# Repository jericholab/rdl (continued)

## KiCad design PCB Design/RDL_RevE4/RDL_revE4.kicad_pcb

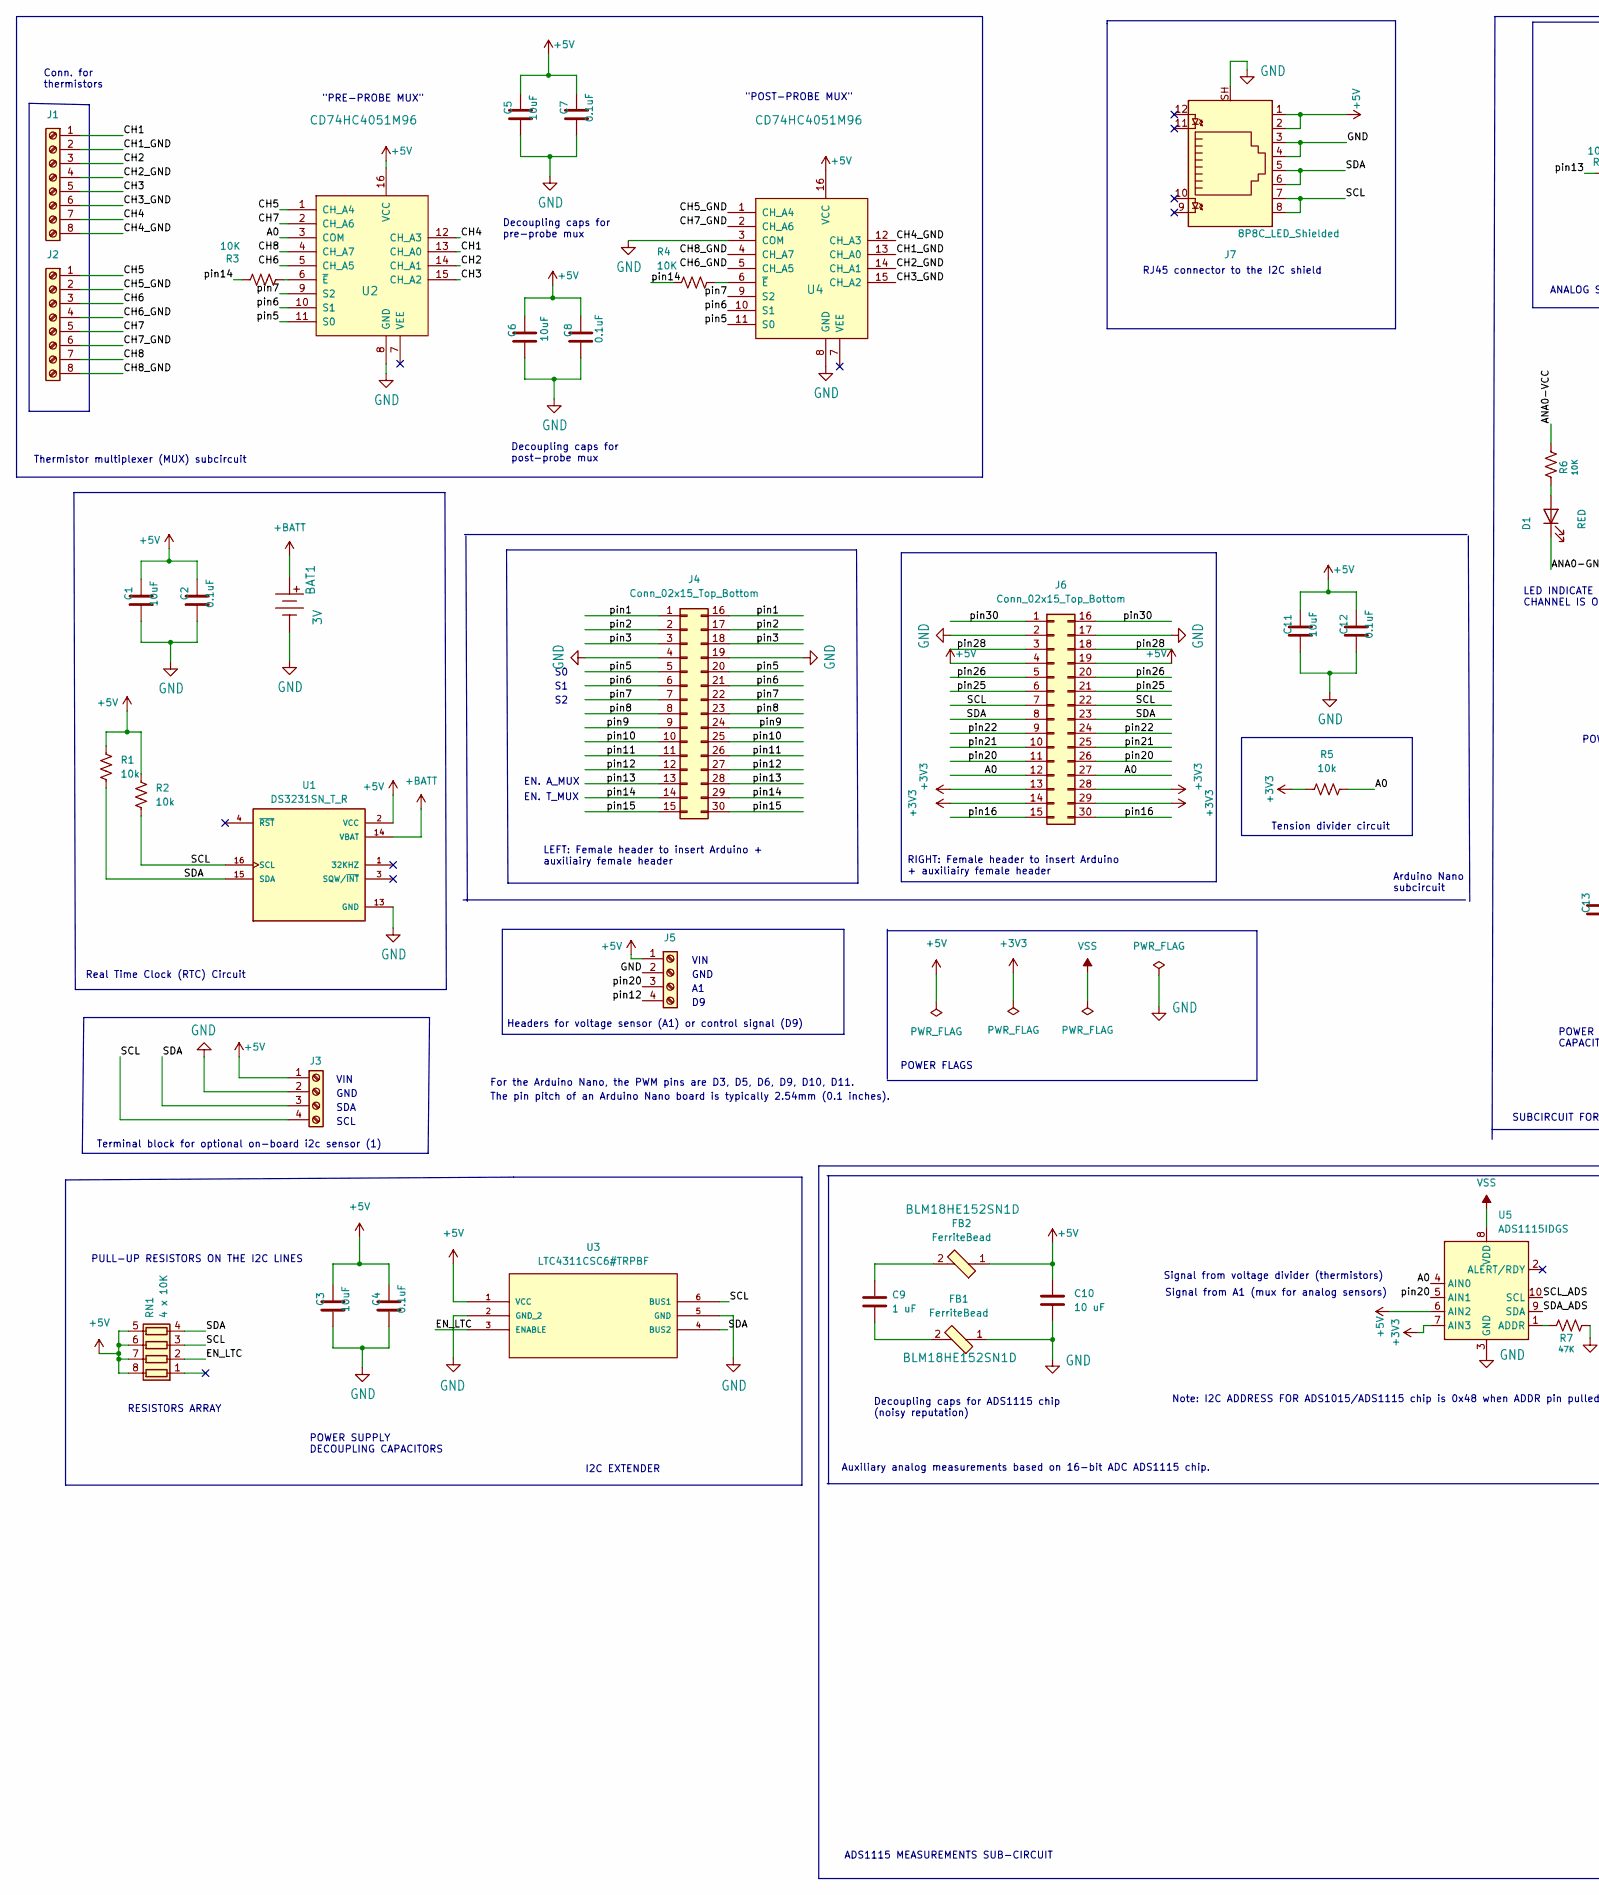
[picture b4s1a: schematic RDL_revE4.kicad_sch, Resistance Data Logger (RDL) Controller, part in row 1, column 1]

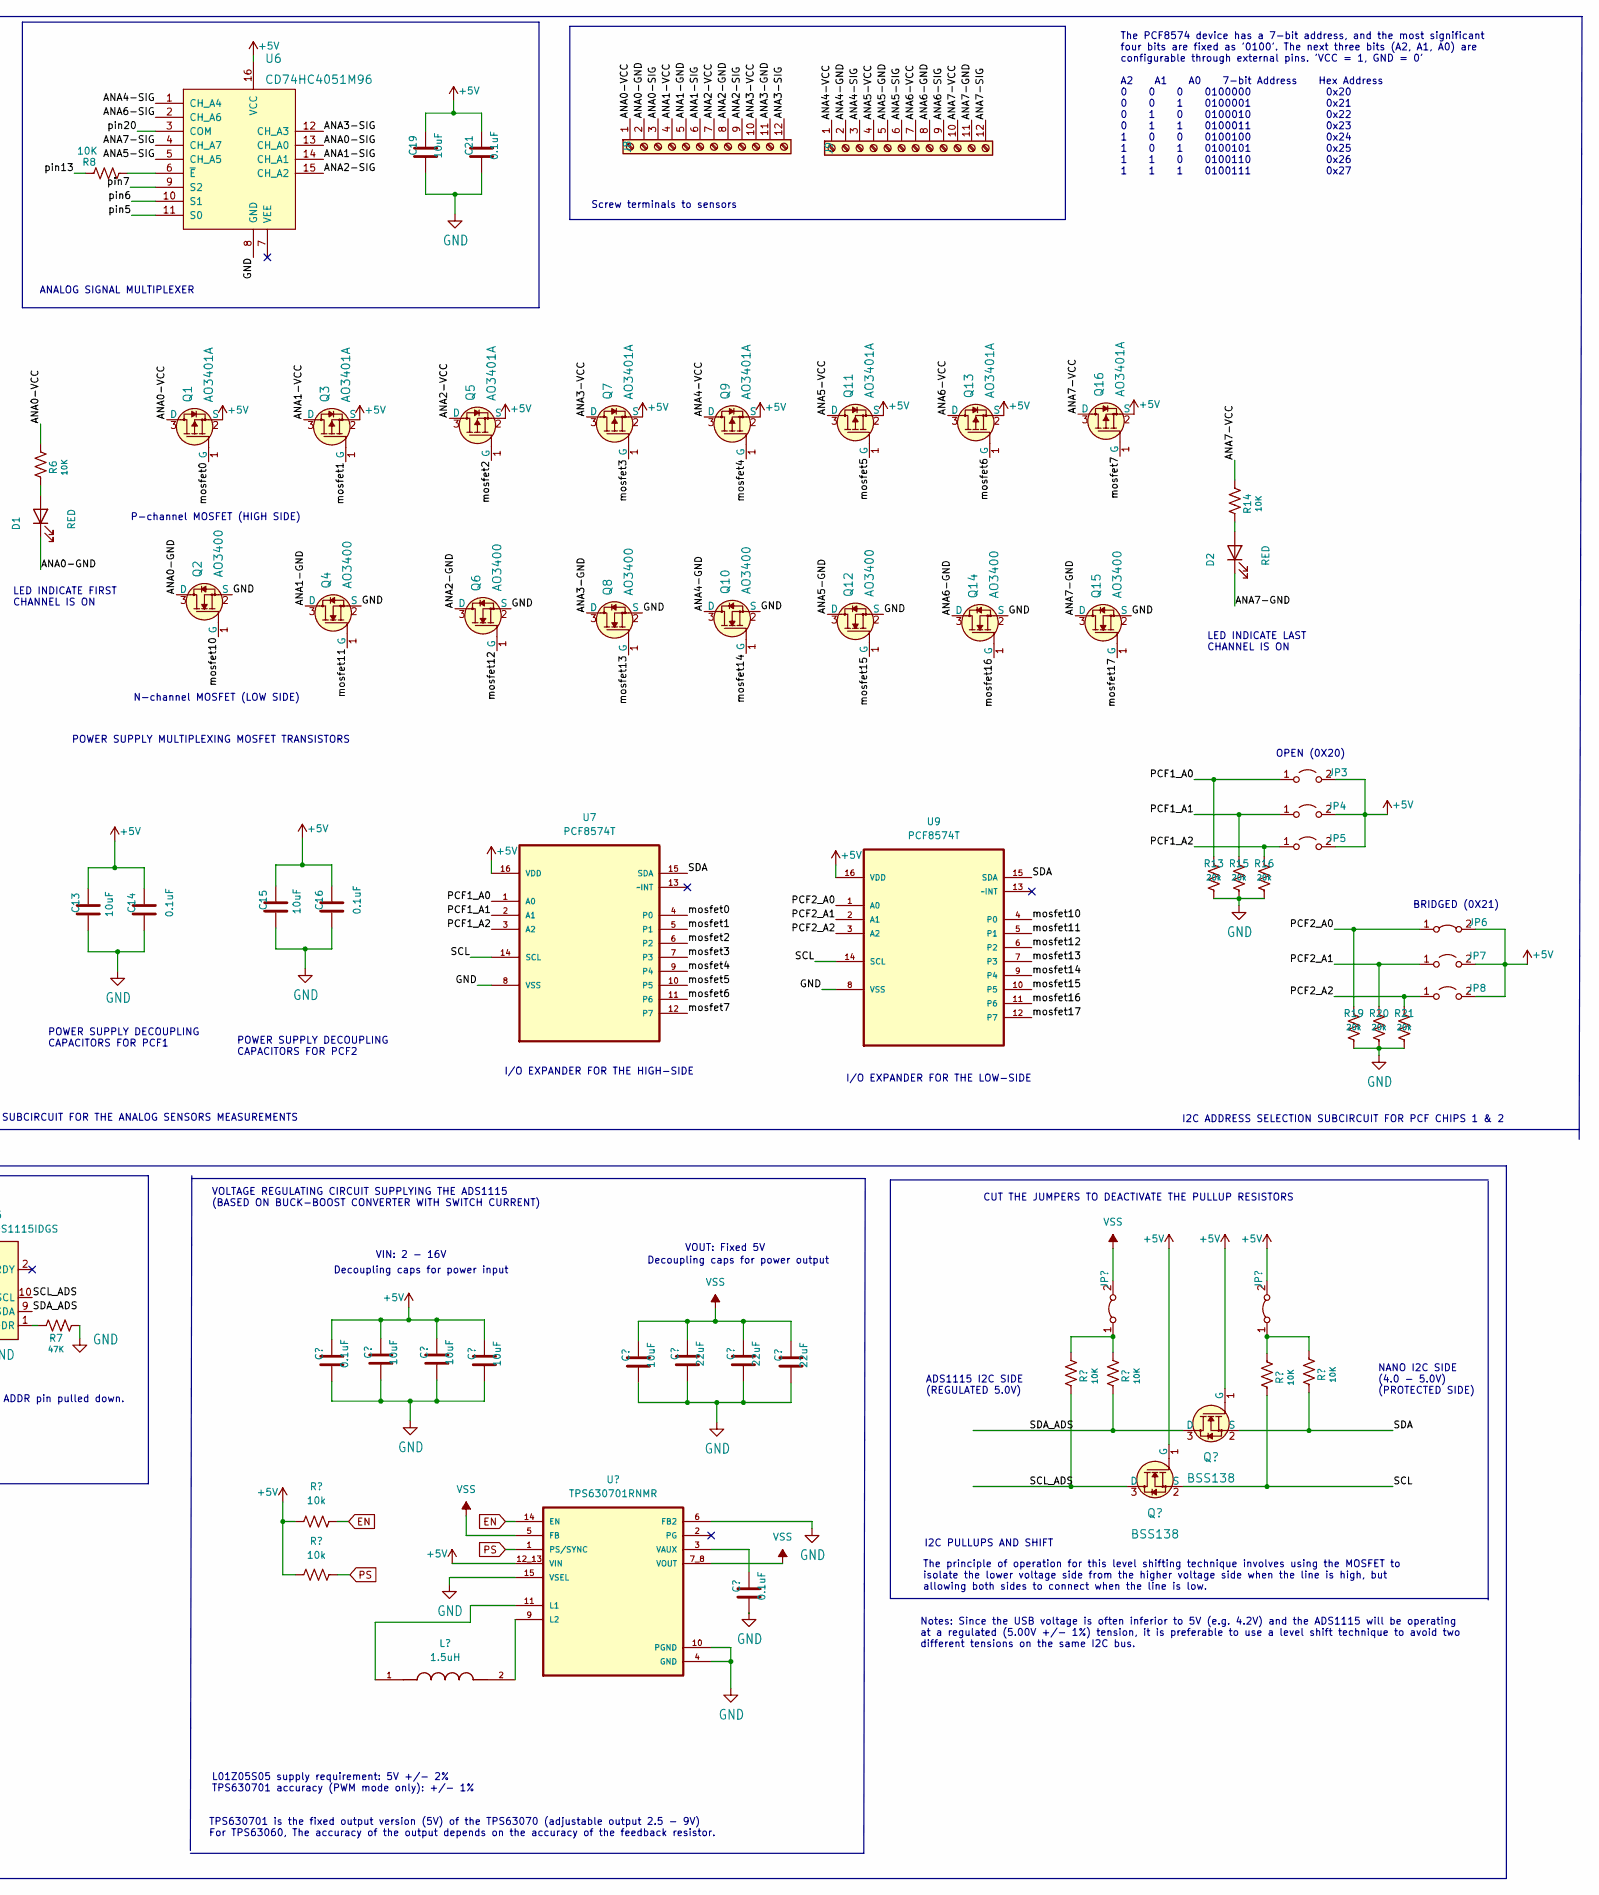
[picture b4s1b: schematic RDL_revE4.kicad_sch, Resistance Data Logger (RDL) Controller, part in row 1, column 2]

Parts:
BAT1: 3V; BatteryHolder_Keystone_3000_1x12mm-Edited; MPN BS-7; Digi-Key_PN BS-7-ND
C1, C3, C5, C6, C11, C13, C15, C18, C19, C20, C22, C23: 10uF; C_0805_2012Metric; LCSC C440198
C2, C4, C7, C8, C12, C14, C16, C17, C21, C26: 0.1uF; C_0805_2012Metric; LCSC C49678
C9: 1 uF; C_1206_3216Metric; LCSC C1848
C10: 10 uF; C_1206_3216Metric; LCSC C13585
C24, C25, C27: 22uF; C_0805_2012Metric; LCSC C45783
D1, D2: RED; D_0603_1608Metric; LCSC C2286
FB1, FB2: FerriteBead; 0603; MPN BLM18HE152SN1D; Digi-Key_PN 490-5216-1-ND
J1: Screw_Terminal_01x08; Term_Block_1x8_P5mm; LCSC C395863
J2: Term_Block_1x8_P5mm; LCSC C395863
J3: Screw_Terminal_01x04; Term_Block_1x4_P5mm; LCSC C424682
J4, J6: Conn_02x15_Top_Bottom; PinHeader_2x15_P2.54mm_Vertical_Jericho; LCSC C7499350
J5: Term_Block_1x4_P5mm; LCSC C424682
J7: 8P8C_LED_Shielded; RJ45_Amphenol_RJHSE538X; LCSC C386757
J8, J9: Screw_Terminal_01x12; TerminalBlock_Phoenix_PT-1,5-12-5.0-H_1x12_P5.00mm_Horizont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; LCSC C5290376
JP1, JP2: Jumper_2_Bridged; SolderJumper-2_P1.3mm_Bridged_Pad1.0x1.5mm-Edited
JP3, JP4, JP5, JP7, JP8: Jumper_2_Bridged; SolderJumper-2_P1.3mm_Open_TrianglePad1.0x1.5mm
JP6: Jumper_2_Bridged; SolderJumper-2_P1.3mm_Bridged_Pad1.0x1.5mm
L1: 1.5uH; IND_XFL4020-152MEC; PARTREV 11/02/18; LCSC C167802
Q1, Q3, Q5, Q7, Q9, Q11, Q13, Q16: AO3401A; SOT-23-3; MPN AO3401A; Digi-Key_PN 785-1001-1-ND
Q2, Q4, Q6, Q8, Q10, Q12, Q14, Q15: AO3400; SOT-23-3; MPN 2N7002; Digi-Key_PN 2N7002NCT-ND
Q17, Q18: BSS138; SOT-23-3; MPN BSS138; Digi-Key_PN BSS138CT-ND
R1, R2, R9, R10: 10k; R_1206_3216Metric; LCSC C17902
R3, R4, R8: 10K; R_1206_3216Metric; LCSC C17902
R5: 10k; R_1206_3216Metric_Pad1.30x1.75mm_HandSolder; LCSC C319946
R6, R11, R12, R14, R17, R18: 10K; R_0805_2012Metric; LCSC C17414
R7: 47K; R_0805_2012Metric; LCSC C17713
R13, R15, R16, R19, R20, R21: 20k; R_0805_2012Metric; LCSC C4328
RN1: 4 x 10K; R_Array_Convex_4x0603; LCSC C29718
U1: DS3231SN_T_R; SOIC127P1032X265-16N; LCSC C9866
U2, U4, U6: CD74HC4051M96; SOP-16_3.9x9.9mm_P1.27mm-Edited; MPN CD74HC4051E; Digi-Key_PN 296-12810-5-ND
U3: LTC4311CSC6#TRPBF; SC70-SC6; MANUFACTURER_PART_NUMBER ltc4311csc6#pbf; LCSC C580856
U5: ADS1115IDGS; TSSOP-10_3x3mm_P0.5mm; LCSC C37593
U7, U9: PCF8574T; SOIC127P1032X265-16N_FRED_MODIFIED; MPN PCF8574T; LCSC C2987288
U8: TPS630701RNMR; VREG_TPS63070RNMR; LCSC C2876599

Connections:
+3V3: J6.13, J6.14, J6.28, J6.29, R5.2, U5.7 (AIN3)
+5V: C1.1, C2.1, C3.1, C4.1, C5.1, C6.1, C7.1, C8.1, C10.1, C11.1, C12.1, C13.1, C14.1, C15.1, C16.1, C17.1, C18.1, C19.1, C20.1, C21.1, C22.1, FB2.1, J3.1, J5.1, J6.4, J6.19, J7.1, J7.2, JP2.2 (B), JP3.2 (B), JP4.2 (B), JP5.2 (B), JP6.2 (B), JP7.2 (B), JP8.2 (B), Q1.2 (S), Q3.2 (S), Q5.2 (S), Q7.2 (S), Q9.2 (S), Q11.2 (S), Q13.2 (S), Q16.2 (S), Q17.1 (G), Q18.1 (G), R1.1, R2.1, R9.2, R10.1, RN1.5 (R4.2), RN1.6 (R3.2), RN1.7 (R2.2), RN1.8 (R1.2), U1.2 (VCC), U2.16 (VCC), U3.1 (VCC), U4.16 (VCC), U5.6 (AIN2), U6.16 (VCC), U7.16 (VDD), U8.12_13 (VIN), U9.16 (VDD)
+BATT: BAT1.Pos, U1.14 (VBAT)
/A0: J6.12, J6.27, R5.1, U2.3 (COM), U5.4 (AIN0)
/ANA0-GND: D1.1 (K), J8.2, Q2.3 (D)
/ANA0-SIG: J8.3, U6.13 (CH_A0)
/ANA0-VCC: J8.1, Q1.3 (D), R6.2
/ANA1-GND: J8.5, Q4.3 (D)
/ANA1-SIG: J8.6, U6.14 (CH_A1)
/ANA1-VCC: J8.4, Q3.3 (D)
/ANA2-GND: J8.8, Q6.3 (D)
/ANA2-SIG: J8.9, U6.15 (CH_A2)
/ANA2-VCC: J8.7, Q5.3 (D)
/ANA3-GND: J8.11, Q8.3 (D)
/ANA3-SIG: J8.12, U6.12 (CH_A3)
/ANA3-VCC: J8.10, Q7.3 (D)
/ANA4-GND: J9.2, Q10.3 (D)
/ANA4-SIG: J9.3, U6.1 (CH_A4)
/ANA4-VCC: J9.1, Q9.3 (D)
/ANA5-GND: J9.5, Q12.3 (D)
/ANA5-SIG: J9.6, U6.5 (CH_A5)
/ANA5-VCC: J9.4, Q11.3 (D)
/ANA6-GND: J9.8, Q14.3 (D)
/ANA6-SIG: J9.9, U6.2 (CH_A6)
/ANA6-VCC: J9.7, Q13.3 (D)
/ANA7-GND: D2.1 (K), J9.11, Q15.3 (D)
/ANA7-SIG: J9.12, U6.4 (CH_A7)
/ANA7-VCC: J9.10, Q16.3 (D), R14.2
/CH1: J1.1, U2.13 (CH_A0)
/CH1_GND: J1.2, U4.13 (CH_A0)
/CH2: J1.3, U2.14 (CH_A1)
/CH2_GND: J1.4, U4.14 (CH_A1)
/CH3: J1.5, U2.15 (CH_A2)
/CH3_GND: J1.6, U4.15 (CH_A2)
/CH4: J1.7, U2.12 (CH_A3)
/CH4_GND: J1.8, U4.12 (CH_A3)
/CH5: J2.1, U2.1 (CH_A4)
/CH5_GND: J2.2, U4.1 (CH_A4)
/CH6: J2.3, U2.5 (CH_A5)
/CH6_GND: J2.4, U4.5 (CH_A5)
/CH7: J2.5, U2.2 (CH_A6)
/CH7_GND: J2.6, U4.2 (CH_A6)
/CH8: J2.7, U2.4 (CH_A7)
/CH8_GND: J2.8, U4.4 (CH_A7)
/EN_LTC: RN1.2 (R2.1), U3.3 (ENABLE)
/PCF1_A0: JP3.1 (A), R13.1, U7.1 (A0)
/PCF1_A1: JP4.1 (A), R15.1, U7.2 (A1)
/PCF1_A2: JP5.1 (A), R16.1, U7.3 (A2)
/PCF2_A0: JP6.1 (A), R19.1, U9.1 (A0)
/PCF2_A1: JP7.1 (A), R20.1, U9.2 (A1)
/PCF2_A2: JP8.1 (A), R21.1, U9.3 (A2)
/SCL: J3.4, J6.7, J6.22, J7.7, J7.8, Q17.2 (S), R2.2, R17.1, RN1.3 (R3.1), U1.16 (SCL), U3.6 (BUS1), U7.14 (SCL), U9.14 (SCL)
/SCL_ADS: Q17.3 (D), R11.1, U5.10 (SCL)
/SDA: J3.3, J6.8, J6.23, J7.5, J7.6, Q18.2 (S), R1.2, R18.1, RN1.4 (R4.1), U1.15 (SDA), U3.4 (BUS2), U7.15 (SDA), U9.15 (SDA)
/SDA_ADS: Q18.3 (D), R12.1, U5.9 (SDA)
/mosfet0: Q1.1 (G), U7.4 (P0)
/mosfet1: Q3.1 (G), U7.5 (P1)
/mosfet2: Q5.1 (G), U7.6 (P2)
/mosfet3: Q7.1 (G), U7.7 (P3)
/mosfet4: Q9.1 (G), U7.9 (P4)
/mosfet5: Q11.1 (G), U7.10 (P5)
/mosfet6: Q13.1 (G), U7.11 (P6)
/mosfet7: Q16.1 (G), U7.12 (P7)
/mosfet10: Q2.1 (G), U9.4 (P0)
/mosfet11: Q4.1 (G), U9.5 (P1)
/mosfet12: Q6.1 (G), U9.6 (P2)
/mosfet13: Q8.1 (G), U9.7 (P3)
/mosfet14: Q10.1 (G), U9.9 (P4)
/mosfet15: Q12.1 (G), U9.10 (P5)
/mosfet16: Q14.1 (G), U9.11 (P6)
/mosfet17: Q15.1 (G), U9.12 (P7)
/pin1: J4.1, J4.16
/pin2: J4.2, J4.17
/pin3: J4.3, J4.18
/pin5: J4.5, J4.20, U2.11 (S0), U4.11 (S0), U6.11 (S0)
/pin6: J4.6, J4.21, U2.10 (S1), U4.10 (S1), U6.10 (S1)
/pin7: J4.7, J4.22, U2.9 (S2), U4.9 (S2), U6.9 (S2)
/pin8: J4.8, J4.23
/pin9: J4.9, J4.24
/pin10: J4.10, J4.25
/pin11: J4.11, J4.26
/pin12: J4.12, J4.27, J5.4
/pin13: J4.13, J4.28, R8.1
/pin14: J4.14, J4.29, R3.2, R4.2
/pin15: J4.15, J4.30
/pin16: J6.15, J6.30
/pin20: J5.3, J6.11, J6.26, U5.5 (AIN1), U6.3 (COM)
/pin21: J6.10, J6.25
/pin22: J6.9, J6.24
/pin25: J6.6, J6.21
/pin26: J6.5, J6.20
/pin28: J6.3, J6.18
/pin30: J6.1, J6.16
EN: R9.1, U8.14 (EN)
GND: BAT1.Neg, C1.2, C2.2, C3.2, C4.2, C5.2, C6.2, C7.2, C8.2, C10.2, C11.2, C12.2, C13.2, C14.2, C15.2, C16.2, C17.2, C18.2, C19.2, C20.2, C21.2, C22.2, C23.2, C24.2, C25.2, C26.2, C27.2, FB1.1, J3.2, J4.4, J4.19, J5.2, J6.2, J6.17, J7.3, J7.4, J7.SH, Q2.2 (S), Q4.2 (S), Q6.2 (S), Q8.2 (S), Q10.2 (S), Q12.2 (S), Q14.2 (S), Q15.2 (S), R7.2, R13.2, R15.2, R16.2, R19.2, R20.2, R21.2, U1.13 (GND), U2.8 (GND), U3.2 (GND_2), U3.5 (GND), U4.3 (COM), U4.8 (GND), U5.3 (GND), U6.8 (GND), U7.8 (VSS), U8.4 (GND), U8.6 (FB2), U8.10 (PGND), U8.15 (VSEL), U9.8 (VSS)
unnamed: C9.1, FB2.2
unnamed: C9.2, FB1.2
unnamed: D1.2 (A), R6.1
unnamed: D2.2 (A), R14.1
unnamed: JP1.1 (A), R11.2, R12.2
unnamed: JP2.1 (A), R17.2, R18.2
unnamed: R3.1, U2.6 (~E)
unnamed: R4.1, U4.6 (~E)
unnamed: R7.1, U5.1 (ADDR)
unnamed: R8.2, U6.6 (~E)
unnamed: L1.1, U8.11 (L1)
unnamed: L1.2, U8.9 (L2)
unnamed: C26.1, U8.3 (VAUX)
PS: R10.2, U8.1 (PS/SYNC)
VSS: C23.1, C24.1, C25.1, C27.1, JP1.2 (B), U5.8 (VDD), U8.5 (FB), U8.7_8 (VOUT)

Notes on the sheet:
EN. T_MUX
Thermistor multiplexer (MUX) subcircuit
N-channel MOSFET (LOW SIDE)
Arduino Nano subcircuit
I/O EXPANDER FOR THE HIGH-SIDE
The principle of operation for this level shifting technique involves using the MOSFET to isolate the lower voltage side from the higher voltage side when the line is high, but allowing both sides to connect when the line is low.
Notes: Since the USB voltage is often inferior to 5V (e.g. 4.2V) and the ADS1115 will be operating at a regulated (5.00V +/- 1%) tension, it is preferable to use a level shift technique to avoid two different tensions on the same I2C bus.
L01Z05S05 supply requirement: 5V +/- 2% TPS630701 accuracy (PWM mode only): +/- 1%
LEFT: Female header to insert Arduino + auxiliairy female header
P-channel MOSFET (HIGH SIDE)
POWER SUPPLY DECOUPLING CAPACITORS
Decoupling caps for ADS1115 chip (noisy reputation)
SCL
LED INDICATE FIRST CHANNEL IS ON
Terminal block for optional on-board i2c sensor (1)
Real Time Clock (RTC) Circuit
Note: I2C ADDRESS FOR ADS1015/ADS1115 chip is 0x48 when ADDR pin pulled down.
TPS630701 is the fixed output version (5V) of the TPS63070 (adjustable output 2.5 - 9V) For TPS63060, The accuracy of the output depends on the accuracy of the feedback resistor.
GND
VIN: 2 - 16V
Decoupling caps for power output
Auxiliary analog measurements based on 16-bit ADC ADS1115 chip.
POWER SUPPLY MULTIPLEXING MOSFET TRANSISTORS
BRIDGED (0X21)
LED INDICATE LAST CHANNEL IS ON
Decoupling caps for post-probe mux
Signal from A1 (mux for analog sensors)
VIN
"POST-PROBE MUX"
I2C PULLUPS AND SHIFT
SDA
PULL-UP RESISTORS ON THE I2C LINES
"PRE-PROBE MUX"
ADS1115 MEASUREMENTS SUB-CIRCUIT
Conn. for thermistors
Decoupling caps for power input
I2C ADDRESS SELECTION SUBCIRCUIT FOR PCF CHIPS 1 & 2
VOLTAGE REGULATING CIRCUIT SUPPLYING THE ADS1115 (BASED ON BUCK-BOOST CONVERTER WITH SWITCH CURRENT)
The pin pitch of an Arduino Nano board is typically 2.54mm (0.1 inches).
RESISTORS ARRAY

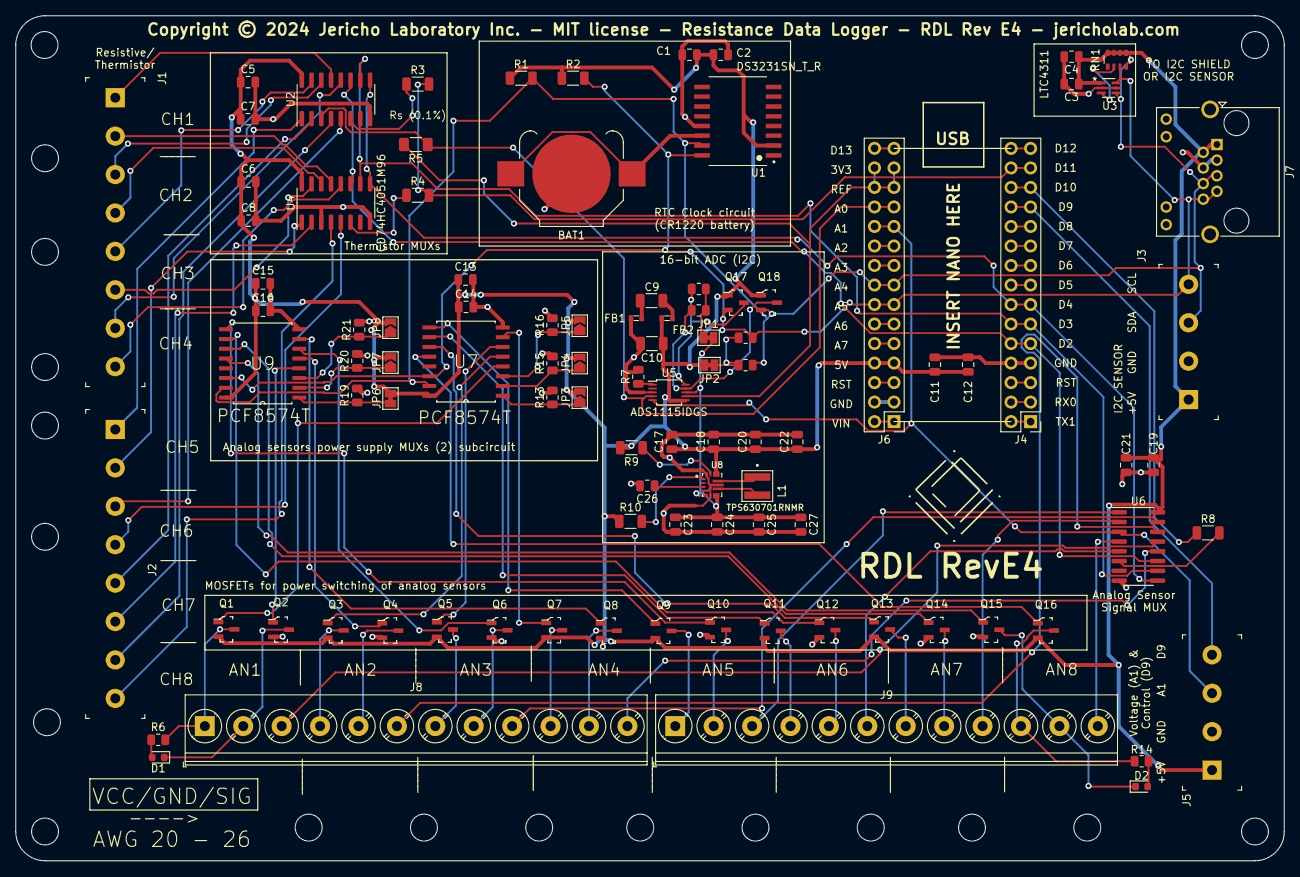
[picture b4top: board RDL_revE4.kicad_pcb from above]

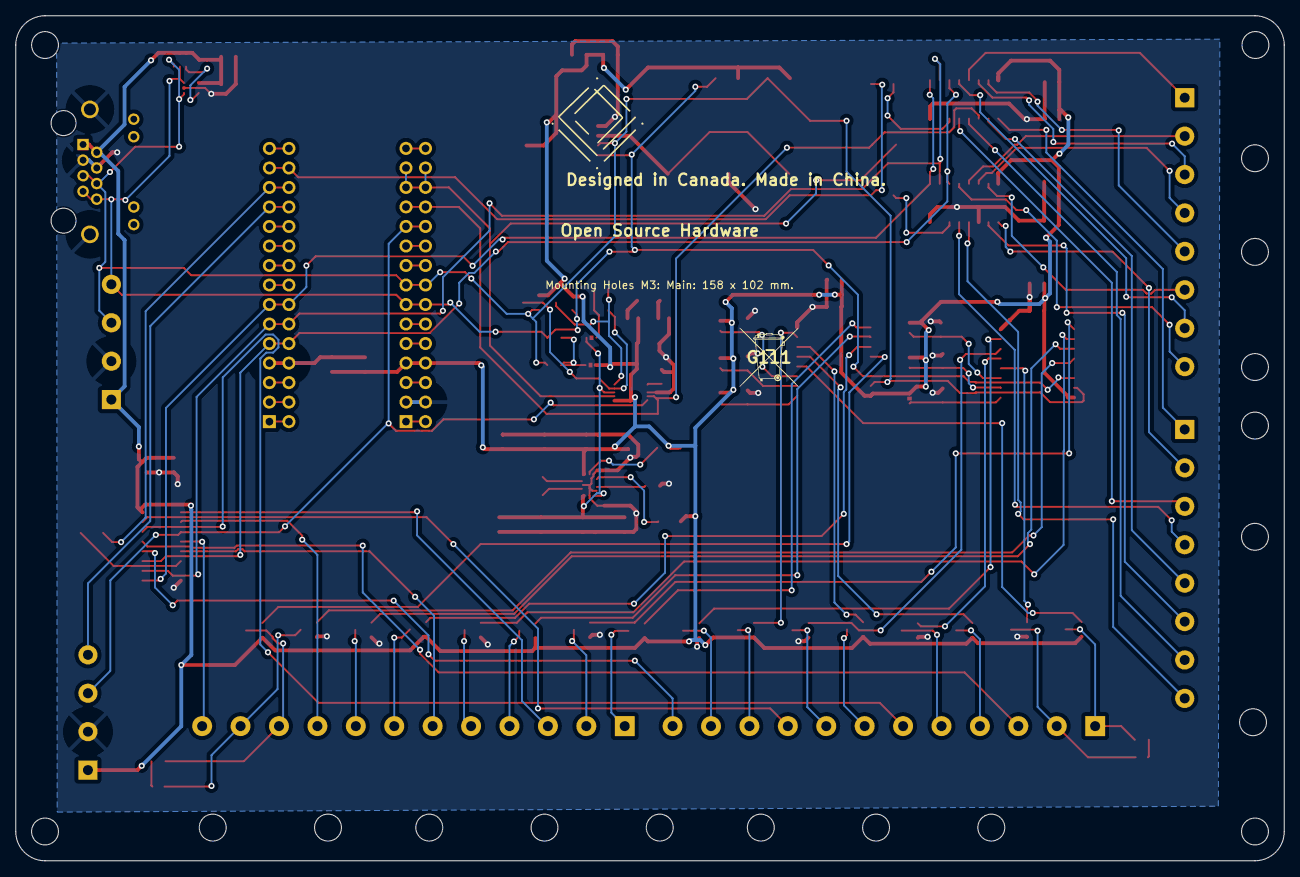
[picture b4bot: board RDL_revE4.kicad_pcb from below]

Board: 2 copper layers, 165.1 x 110.0 mm, 120 parts (2 on the bottom side), 110 nets.

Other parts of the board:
G111: LOGO; Do not throw to garbage logo WEEE2
G222, G222#2: LOGO; jericho-logo-kicad
H6, H7, H51: MountingHole_3.5mm
REF3, REF4, REF5, REF6, REF7, REF8, REF9, REF10, REF11, REF13, REF14, REF15, REF16, REF17, REF18: MountingHole_3.5mm

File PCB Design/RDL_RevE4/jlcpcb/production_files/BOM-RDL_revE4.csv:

Comment,Designator,Footprint,LCSC
CD74HC4051M96,"U2,U4,U6",SOP-16_3.9x9.9mm_P1.27mm-Edited,C132065
10 uF,C10,C_1206_3216Metric,C13585
AO3401A,"Q1,Q11,Q13,Q16,Q3,Q5,Q7,Q9",SOT-23-3,C15127
1.5uH,L1,IND_XFL4020-152MEC,C167802
10K,"R11,R12,R14,R17,R18,R6",R_0805_2012Metric,C17414
47K,R7,R_0805_2012Metric,C17713
10k,"R1,R10,R2,R3,R4,R8,R9",R_1206_3216Metric,C17902
1 uF,C9,C_1206_3216Metric,C1848
AO3400,"Q10,Q12,Q14,Q15,Q2,Q4,Q6,Q8",SOT-23-3,C20917
RED,"D1,D2",D_0603_1608Metric,C2286
TPS630701RNMR,U8,VREG_TPS63070RNMR,C2876599
4 x 10K,RN1,R_Array_Convex_4x0603,C29718
PCF8574T,"U7,U9",SOIC127P1032X265-16N_FRED_MODIFIED,C2987288
10k,R5,R_1206_3216Metric_Pad1.30x1.75mm_HandSolder,C319946
ADS1115IDGS,U5,TSSOP-10_3x3mm_P0.5mm,C37593
8P8C_LED_Shielded,J7,RJ45_Amphenol_RJHSE538X,C386757
Screw_Terminal_01x08,"J1,J2",Term_Block_1x8_P5mm,C395863
Screw_Terminal_01x04,"J3,J5",Term_Block_1x4_P5mm,C424682
20k,"R13,R15,R16,R19,R20,R21",R_0805_2012Metric,C4328
10uF,"C1,C11,C13,C15,C18,C19,C20,C22,C23,C3,C5,C6",C_0805_2012Metric,C440198
22uF,"C24,C25,C27",C_0805_2012Metric,C45783
0.1uF,"C12,C14,C16,C17,C2,C21,C26,C4,C7,C8",C_0805_2012Metric,C49678
Screw_Terminal_01x12,"J8,J9","TerminalBlock_Phoenix_PT-1,5-12-5.0-H_1x12_P5.00mm_Horizontal",C5290376
LTC4311CSC6#TRPBF,U3,SC70-SC6,C580856
BSS138,"Q17,Q18",SOT-23-3,C7420339
Conn_02x15_Top_Bottom,"J4,J6",PinHeader_2x15_P2.54mm_Vertical_Jericho,C7499350
FerriteBead,"FB1,FB2",0603,C82155
3V,BAT1,BatteryHolder_Keystone_3000_1x12mm-Edited,C964818
DS3231SN_T_R,U1,SOIC127P1032X265-16N,C9866

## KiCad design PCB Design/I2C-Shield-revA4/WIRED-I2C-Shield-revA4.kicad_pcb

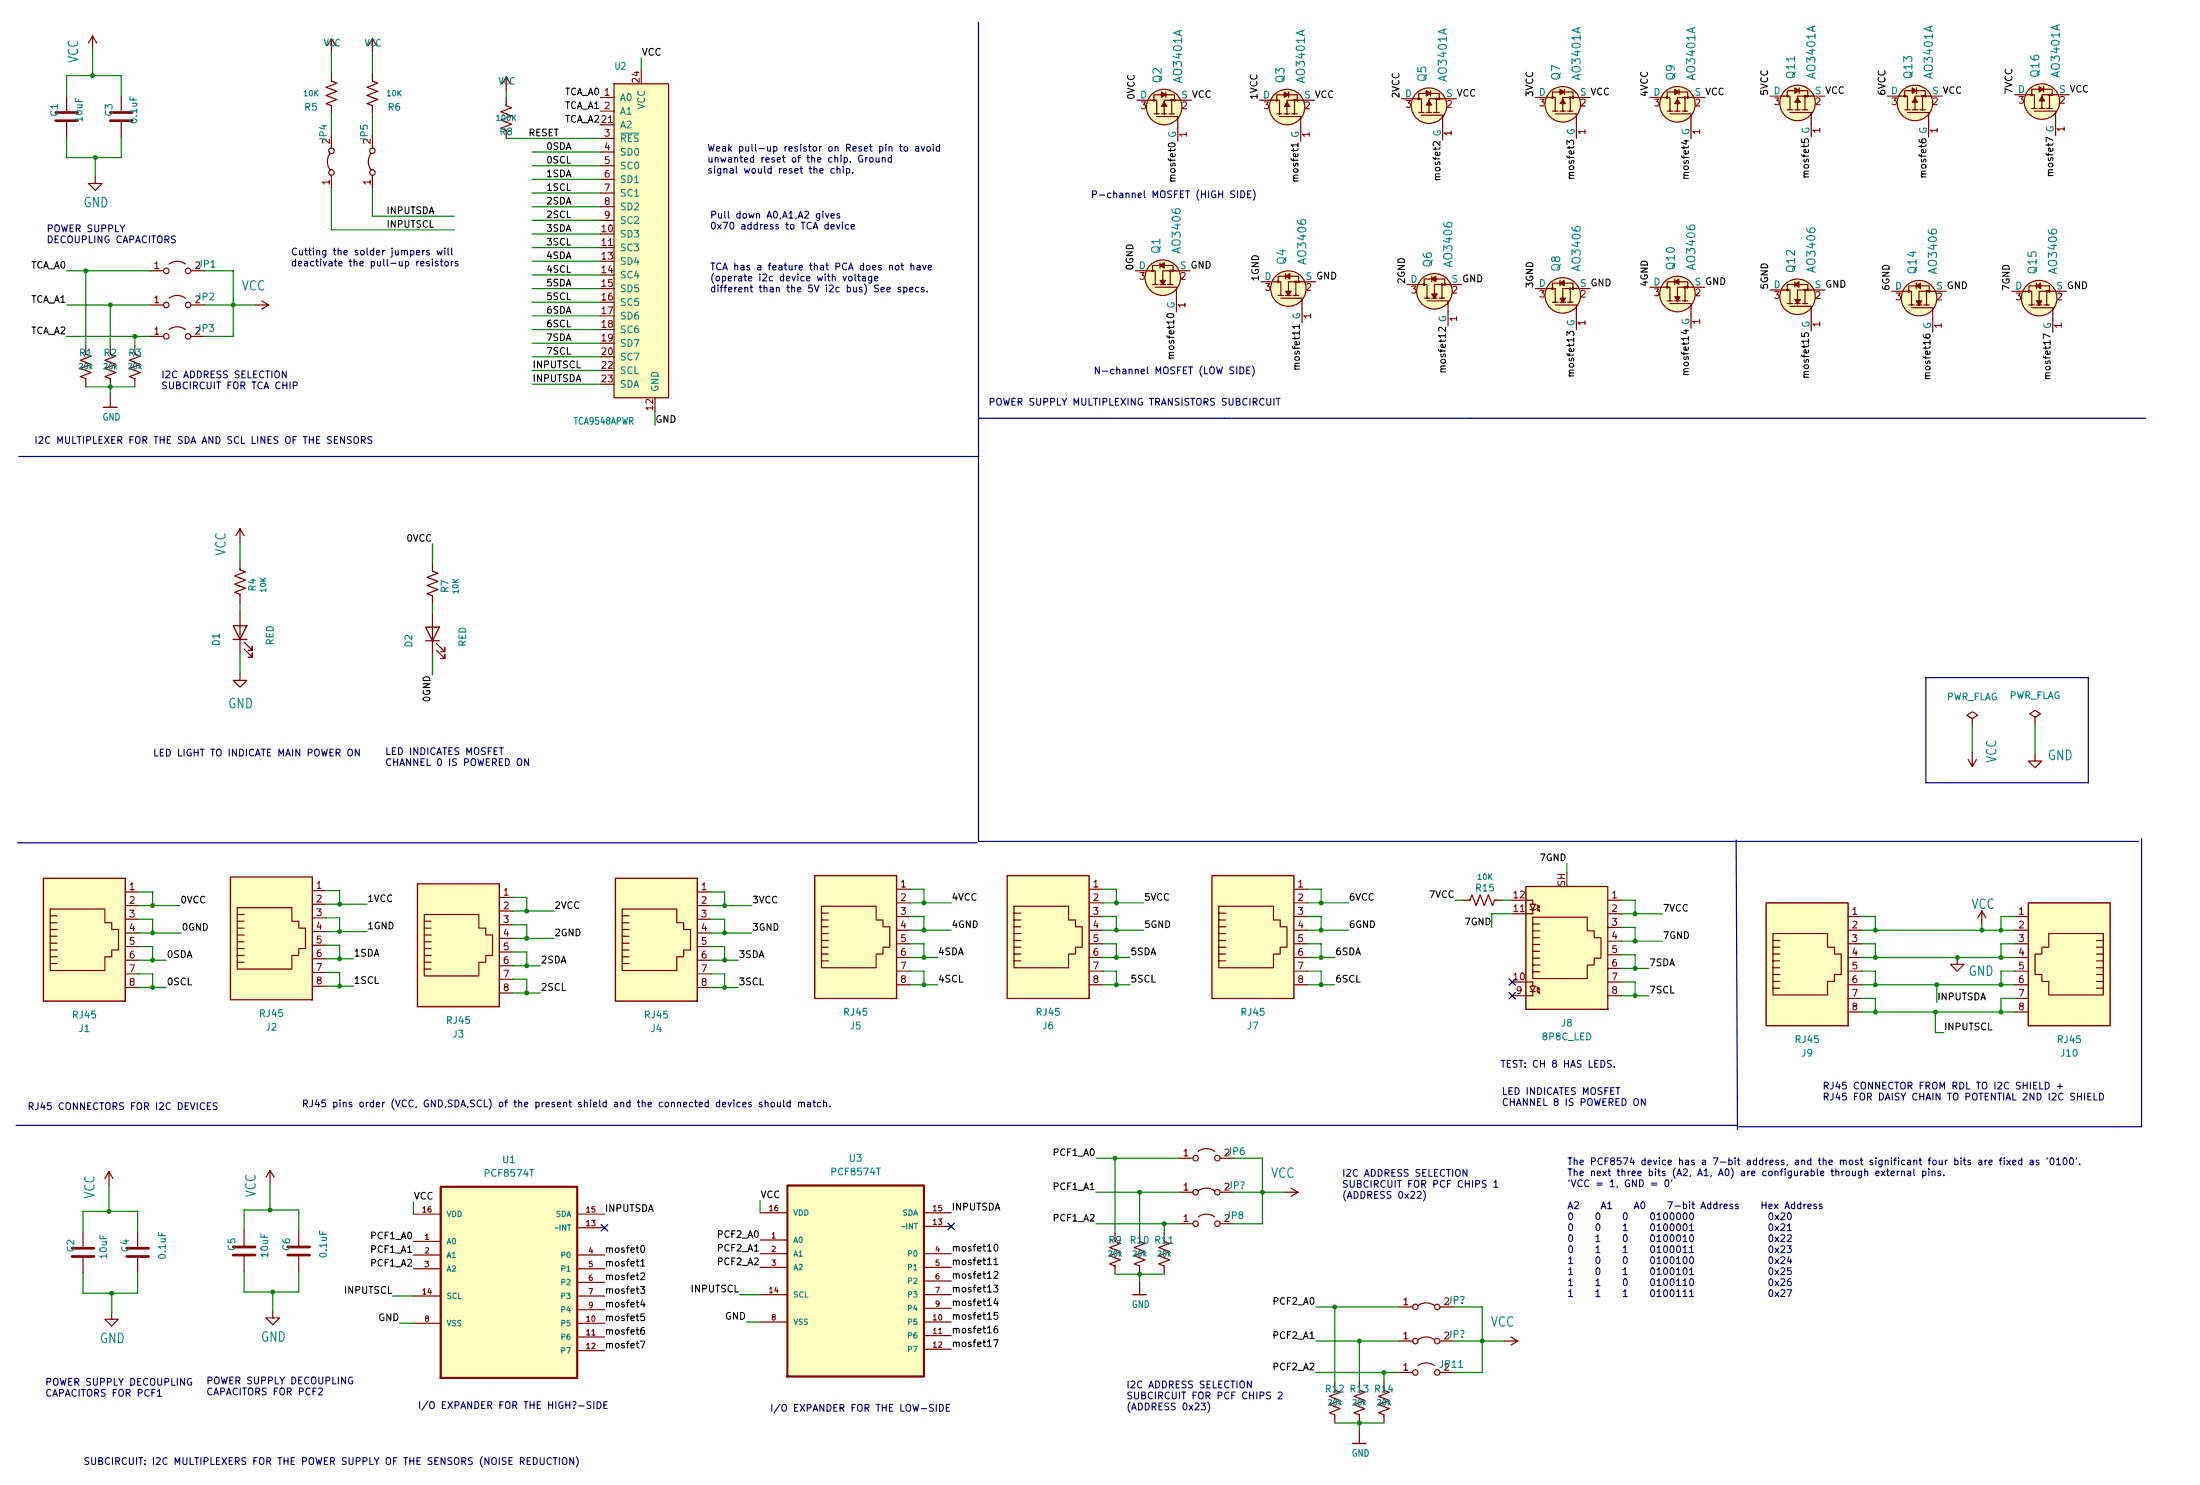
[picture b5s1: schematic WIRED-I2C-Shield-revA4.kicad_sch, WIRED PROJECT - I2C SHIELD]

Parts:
C1, C2, C5: 10uF; C_0805_2012Metric; LCSC C15850
C3, C4, C6: 0.1uF; C_0805_2012Metric; LCSC C49678
D1, D2: RED; D_0603_1608Metric; LCSC C2286
J1, J2, J3, J4, J5, J6, J7, J9, J10: RJ45; RJ45_Amphenol_54602-x08_Horizontal; LCSC C3000197
J8: 8P8C_LED; RJ45_Amphenol_RJHSE538X; LCSC C386757
JP1, JP2, JP3, JP6, JP8, JP11: Jumper_2_Bridged; SolderJumper-2_P1.3mm_Open_Pad1.0x1.5mm
JP4, JP5: Jumper_2_Bridged; SolderJumper-2_P1.3mm_Bridged_Pad1.0x1.5mm
JP7, JP9, JP10: Jumper_2_Bridged; SolderJumper-2_P1.3mm_Bridged_Pad1.0x1.5mm-Edited
Q1, Q4, Q6, Q8, Q10, Q12, Q14, Q15: AO3406; SOT-23-3; MPN 2N7002; Digi-Key_PN 2N7002NCT-ND
Q2, Q3, Q5, Q7, Q9, Q11, Q13, Q16: AO3401A; SOT-23-3; MPN AO3401A; Digi-Key_PN 785-1001-1-ND
R1, R2, R3, R9, R10, R11, R12, R13, R14: 20k; R_0805_2012Metric; LCSC C4328
R4, R5, R6, R7, R15: 10K; R_0805_2012Metric; LCSC C17414
R8: 100K; R_0805_2012Metric; LCSC C149504
U1, U3: PCF8574T; SOIC127P1032X265-16N; MPN PCF8574T; LCSC C2987288
U2: TCA9548APWR; TSSOP-24_W4.40mm; MPN TCA9548APWR; Digi-Key_PN 296-34905-1-ND

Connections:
/0GND: D2.1 (K), J1.3, J1.4, Q1.3 (D)
/0SCL: J1.7, J1.8, U2.5 (SC0)
/0SDA: J1.5, J1.6, U2.4 (SD0)
/0VCC: J1.1, J1.2, Q2.3 (D), R7.2
/1GND: J2.3, J2.4, Q4.3 (D)
/1SCL: J2.7, J2.8, U2.7 (SC1)
/1SDA: J2.5, J2.6, U2.6 (SD1)
/1VCC: J2.1, J2.2, Q3.3 (D)
/2GND: J3.3, J3.4, Q6.3 (D)
/2SCL: J3.7, J3.8, U2.9 (SC2)
/2SDA: J3.5, J3.6, U2.8 (SD2)
/2VCC: J3.1, J3.2, Q5.3 (D)
/3GND: J4.3, J4.4, Q8.3 (D)
/3SCL: J4.7, J4.8, U2.11 (SC3)
/3SDA: J4.5, J4.6, U2.10 (SD3)
/3VCC: J4.1, J4.2, Q7.3 (D)
/4GND: J5.3, J5.4, Q10.3 (D)
/4SCL: J5.7, J5.8, U2.14 (SC4)
/4SDA: J5.5, J5.6, U2.13 (SD4)
/4VCC: J5.1, J5.2, Q9.3 (D)
/5GND: J6.3, J6.4, Q12.3 (D)
/5SCL: J6.7, J6.8, U2.16 (SC5)
/5SDA: J6.5, J6.6, U2.15 (SD5)
/5VCC: J6.1, J6.2, Q11.3 (D)
/6GND: J7.3, J7.4, Q14.3 (D)
/6SCL: J7.7, J7.8, U2.18 (SC6)
/6SDA: J7.5, J7.6, U2.17 (SD6)
/6VCC: J7.1, J7.2, Q13.3 (D)
/7GND: J8.3, J8.4, J8.11, J8.SH, Q15.3 (D)
/7SCL: J8.7, J8.8, U2.20 (SC7)
/7SDA: J8.5, J8.6, U2.19 (SD7)
/7VCC: J8.1, J8.2, Q16.3 (D), R15.2
/INPUTSCL: J9.7, J9.8, J10.7, J10.8, JP4.1 (A), U1.14 (SCL), U2.22 (SCL), U3.14 (SCL)
/INPUTSDA: J9.5, J9.6, J10.5, J10.6, JP5.1 (A), U1.15 (SDA), U2.23 (SDA), U3.15 (SDA)
/PCF1_A0: JP6.1 (A), R9.1, U1.1 (A0)
/PCF1_A1: JP7.1 (A), R10.1, U1.2 (A1)
/PCF1_A2: JP8.1 (A), R11.1, U1.3 (A2)
/PCF2_A0: JP9.1 (A), R12.1, U3.1 (A0)
/PCF2_A1: JP10.1 (A), R13.1, U3.2 (A1)
/PCF2_A2: JP11.1 (A), R14.1, U3.3 (A2)
/RESET: R8.1, U2.3 (~RES)
/TCA_A0: JP1.1 (A), R1.1, U2.1 (A0)
/TCA_A1: JP2.1 (A), R2.1, U2.2 (A1)
/TCA_A2: JP3.1 (A), R3.1, U2.21 (A2)
/mosfet0: Q2.1 (G), U1.4 (P0)
/mosfet1: Q3.1 (G), U1.5 (P1)
/mosfet2: Q5.1 (G), U1.6 (P2)
/mosfet3: Q7.1 (G), U1.7 (P3)
/mosfet4: Q9.1 (G), U1.9 (P4)
/mosfet5: Q11.1 (G), U1.10 (P5)
/mosfet6: Q13.1 (G), U1.11 (P6)
/mosfet7: Q16.1 (G), U1.12 (P7)
/mosfet10: Q1.1 (G), U3.4 (P0)
/mosfet11: Q4.1 (G), U3.5 (P1)
/mosfet12: Q6.1 (G), U3.6 (P2)
/mosfet13: Q8.1 (G), U3.7 (P3)
/mosfet14: Q10.1 (G), U3.9 (P4)
/mosfet15: Q12.1 (G), U3.10 (P5)
/mosfet16: Q14.1 (G), U3.11 (P6)
/mosfet17: Q15.1 (G), U3.12 (P7)
GND: C1.2, C2.2, C3.2, C4.2, C5.2, C6.2, D1.1 (K), J9.3, J9.4, J10.3, J10.4, Q1.2 (S), Q4.2 (S), Q6.2 (S), Q8.2 (S), Q10.2 (S), Q12.2 (S), Q14.2 (S), Q15.2 (S), R1.2, R2.2, R3.2, R9.2, R10.2, R11.2, R12.2, R13.2, R14.2, U1.8 (VSS), U2.12 (GND), U3.8 (VSS)
unnamed: D1.2 (A), R4.1
unnamed: D2.2 (A), R7.1
unnamed: J8.12, R15.1
unnamed: JP4.2 (B), R5.1
unnamed: JP5.2 (B), R6.1
VCC: C1.1, C2.1, C3.1, C4.1, C5.1, C6.1, J9.1, J9.2, J10.1, J10.2, JP1.2 (B), JP2.2 (B), JP3.2 (B), JP6.2 (B), JP7.2 (B), JP8.2 (B), JP9.2 (B), JP10.2 (B), JP11.2 (B), Q2.2 (S), Q3.2 (S), Q5.2 (S), Q7.2 (S), Q9.2 (S), Q11.2 (S), Q13.2 (S), Q16.2 (S), R4.2, R5.2, R6.2, R8.2, U1.16 (VDD), U2.24 (VCC), U3.16 (VDD)

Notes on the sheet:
LED INDICATES MOSFET CHANNEL 8 IS POWERED ON
I/O EXPANDER FOR THE HIGH?-SIDE
Cutting the solder jumpers will deactivate the pull-up resistors
RJ45 CONNECTOR FROM RDL TO I2C SHIELD + RJ45 FOR DAISY CHAIN TO POTENTIAL 2ND I2C SHIELD
LED LIGHT TO INDICATE MAIN POWER ON
I2C ADDRESS SELECTION SUBCIRCUIT FOR TCA CHIP
I2C MULTIPLEXER FOR THE SDA AND SCL LINES OF THE SENSORS
POWER SUPPLY DECOUPLING CAPACITORS
I2C ADDRESS SELECTION SUBCIRCUIT FOR PCF CHIPS 2 (ADDRESS 0x23)
SUBCIRCUIT: I2C MULTIPLEXERS FOR THE POWER SUPPLY OF THE SENSORS (NOISE REDUCTION)
Weak pull-up resistor on Reset pin to avoid unwanted reset of the chip. Ground signal would reset the chip.
POWER SUPPLY DECOUPLING CAPACITORS FOR PCF2
POWER SUPPLY DECOUPLING CAPACITORS FOR PCF1
TCA has a feature that PCA does not have (operate i2c device with voltage different than the 5V i2c bus) See specs.
POWER SUPPLY MULTIPLEXING TRANSISTORS SUBCIRCUIT
I/O EXPANDER FOR THE LOW-SIDE
RJ45 pins order (VCC, GND,SDA,SCL) of the present shield and the connected devices should match.
P-channel MOSFET (HIGH SIDE)
TEST: CH 8 HAS LEDS.
LED INDICATES MOSFET CHANNEL 0 IS POWERED ON
RJ45 CONNECTORS FOR I2C DEVICES
N-channel MOSFET (LOW SIDE)
I2C ADDRESS SELECTION SUBCIRCUIT FOR PCF CHIPS 1 (ADDRESS 0x22)
Pull down A0,A1,A2 gives 0x70 address to TCA device
The PCF8574 device has a 7-bit address, and the most significant four bits are fixed as '0100'. The next three bits (A2, A1, A0) are configurable through external pins. 'VCC = 1, GND = 0' A2 A1 A0 7-bit Address Hex Address 0 0 0 0100000 0x20 0 0 1 0100001 0x21 0 1 0 0100010 0x22 0 1 1 0100011 0x23 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
